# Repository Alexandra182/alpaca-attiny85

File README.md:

# alpaca-attiny85
A cute PCB alpaca with a rainbow tail and glowing cheeks.

PCBs provided by [JLCPCB](https://jlcpcb.com/).

More details [here](https://hackaday.io/project/178344-alpaca-attiny85-breakout-board).

*The original SVG this project is based on was bought from ©Sudowoodo on Can Stock Photo Inc.*

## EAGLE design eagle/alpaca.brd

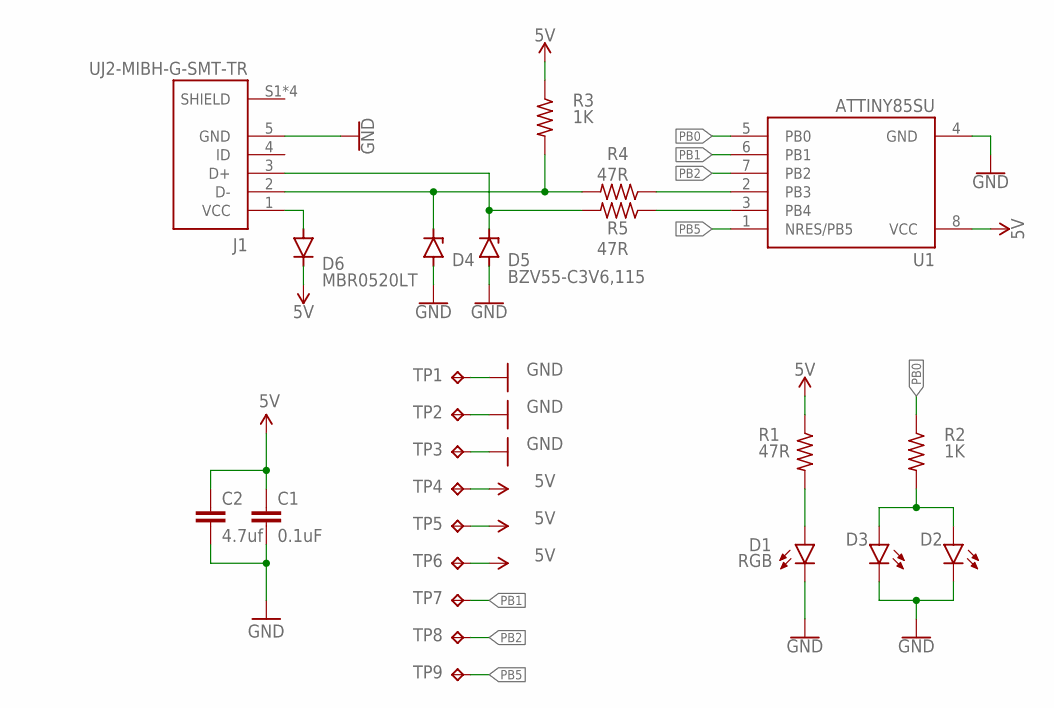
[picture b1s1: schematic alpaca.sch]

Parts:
C1: 0.1uF; C0805K
C2: 4.7uf; C0805K
D1: RGB; LED_3MM-NS
D2, D3: LEDCHIPLED_1206; CHIPLED_1206
D4, D5: BZV55-C3V6,115; SOD80C
D6: MBR0520LT; SOD123
J1: UJ2-MIBH-G-SMT-TR; CUI_UJ2-MIBH-G-SMT-TR
R1, R4, R5: 47R; R0603
R2, R3: 1K; R0603
TP1, TP2, TP3, TP4, TP5, TP6, TP7, TP8, TP9: TPTP13R; TP13R
U1: ATTINY85SU; ATTINY85

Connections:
5V: C1.1, C2.1, D6.C, R1.1, R3.1, TP4.TP, TP5.TP, TP6.TP, U1.8 (VCC)
GND: C1.2, C2.2, D1.K (C), D2.C, D3.C, D4.A, D5.A, J1.5 (GND), TP1.TP, TP2.TP, TP3.TP, U1.4 (GND)
unnamed: D1.A, R1.2
unnamed: D4.C, J1.2 (D-), R3.2, R4.2
unnamed: D5.C, J1.3 (D+), R5.2
unnamed: D6.A, J1.1 (VCC)
unnamed: R5.1, U1.3 (PB4)
unnamed: R4.1, U1.2 (PB3)
unnamed: D2.A, D3.A, R2.2
PB0: R2.1, U1.5 (PB0)
PB1: TP7.TP, U1.6 (PB1)
PB2: TP8.TP, U1.7 (PB2)
PB5: TP9.TP, U1.1 (NRES/PB5)

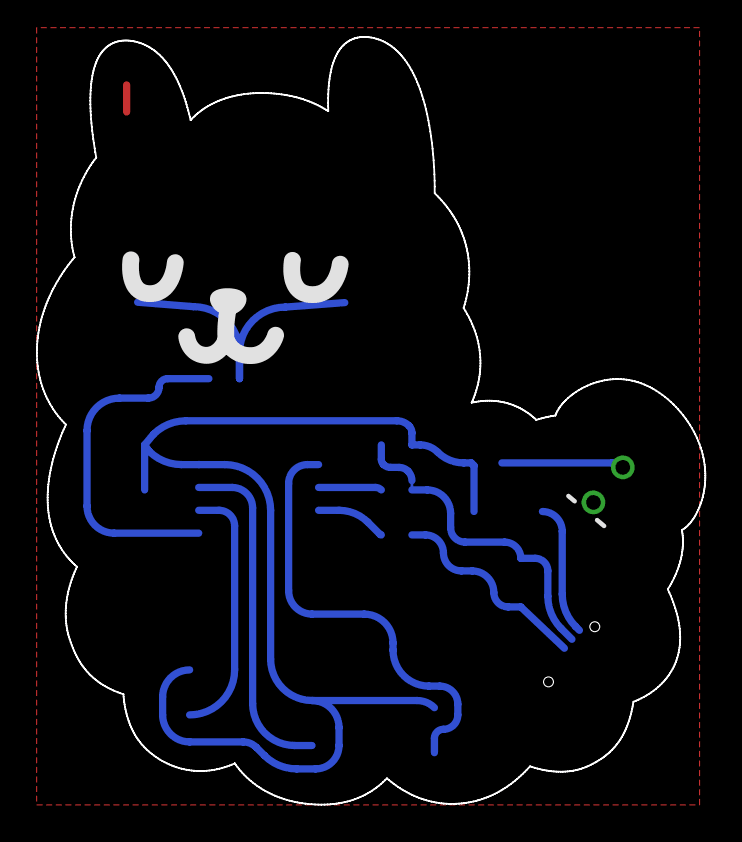
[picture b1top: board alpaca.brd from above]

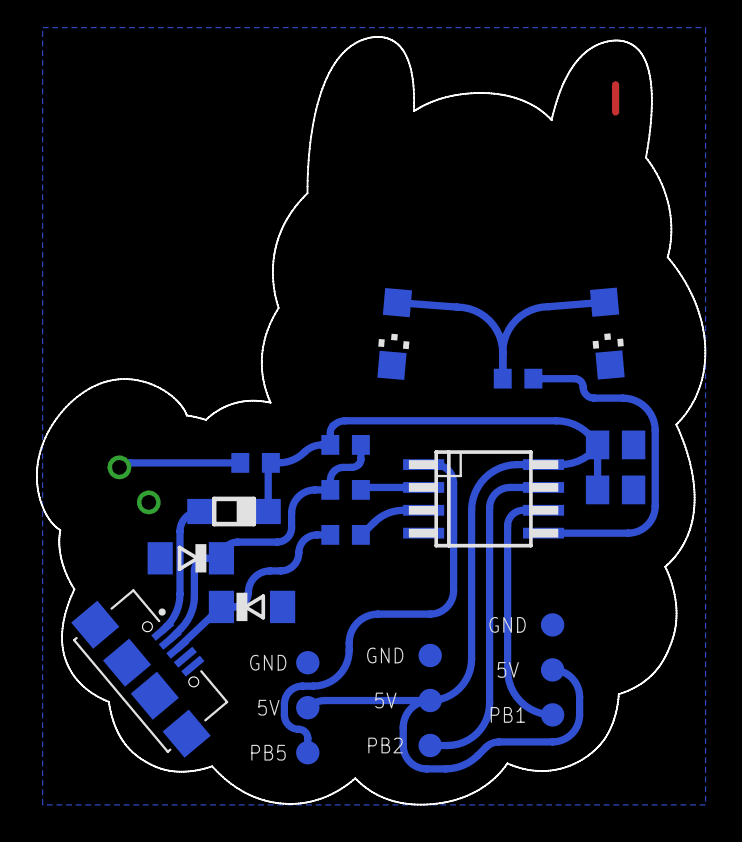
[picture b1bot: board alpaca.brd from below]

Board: 2 copper layers, 37.1 x 42.7 mm, 24 parts (23 on the bottom side), 13 nets.

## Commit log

2021-03-31 added gerber files

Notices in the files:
parts and their libraries:
SparkFun-LED: Licensing: Creative Commons ShareAlike 4.0 International - https://creativecommons.org/licenses/by-sa/4.0
SparkFun: Licensing: CC v3.0 Share-Alike You are welcome to use this library for commercial purposes.
